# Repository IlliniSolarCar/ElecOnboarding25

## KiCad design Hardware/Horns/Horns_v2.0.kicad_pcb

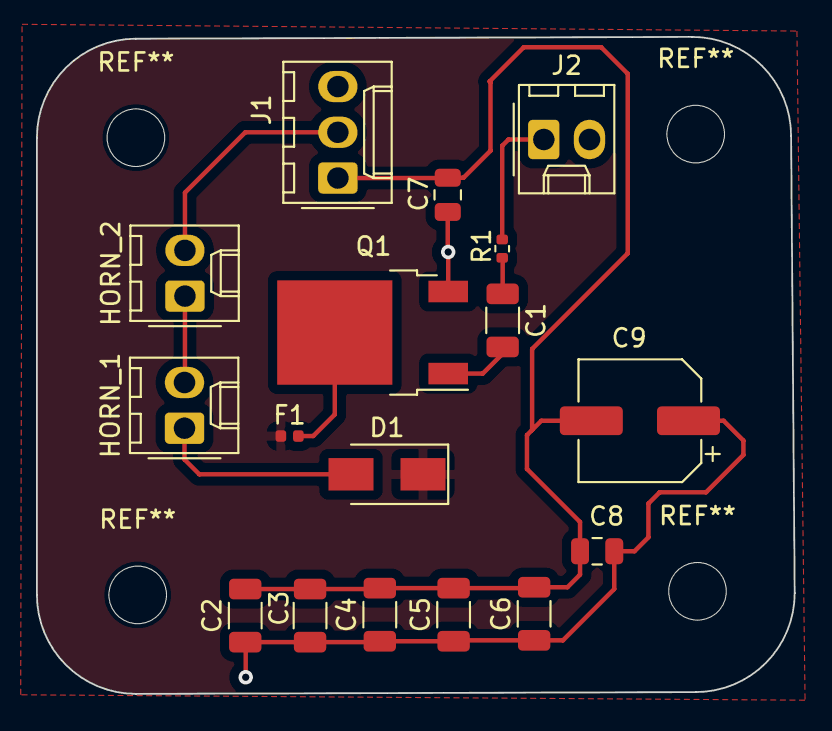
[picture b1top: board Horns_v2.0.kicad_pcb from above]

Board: 2 copper layers, 42.1 x 36.5 mm, 17 parts (0 on the bottom side), 10 nets.

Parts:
C1, C2, C3, C4: 0.1uF; C_1206_3216Metric
C5, C6: 1uF; C_1206_3216Metric
C7, C8: 10uF; C_0805_2012Metric
C9: 100uF; CP_Elec_6.3x5.4_Nichicon
D1: DIODE; D_SMA
F1: 2A; Fuse_0402_1005Metric
HORN_1, HORN_2: Conn_01x02; Molex_KK-254_AE-6410-02A_1x02_P2.54mm_Vertical
J1: Conn_01x03; Molex_KK-254_AE-6410-03A_1x03_P2.54mm_Vertical
J2: Conn_01x02; Molex_KK-254_AE-6410-02A_1x02_P2.54mm_Vertical
Q1: Q_NMOS_GDS; TO-252-2
R1: 1k; R_0402_1005Metric

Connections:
+3V3: D1.1 (K), F1.1
+24V: HORN_2.2, J1.2
/HORN_CONTR: J2.1, R1.1
GND: C2.1, C3.1, C4.1, C5.1, C6.1, C7.1, C8.1, C9.1, J1.3, J2.2, Q1.3 (S)
unnamed: C1.1, R1.2
unnamed: D1.2 (A), HORN_1.1
unnamed: HORN_1.2, HORN_2.1
unnamed: C2.2, C3.2, C4.2, C5.2, C6.2, C7.2, C8.2, C9.2, J1.1
unnamed: F1.2, Q1.2 (D)
unnamed: C1.2, Q1.1 (G)

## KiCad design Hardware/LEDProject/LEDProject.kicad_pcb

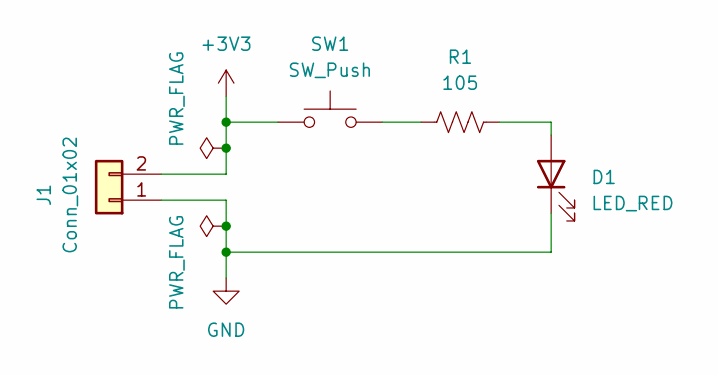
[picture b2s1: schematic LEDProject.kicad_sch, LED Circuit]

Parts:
D1: LED_RED; LED_0603_Symbol_on_F.SilkS
J1: Conn_01x02; Molex_KK-254_AE-6410-02A_1x02_P2.54mm_Vertical; MPN 22272021
R1: 105; R_0603_1608Metric_Pad0.98x0.95mm_HandSolder
SW1: SW_Push; SW_DIP_SPSTx01_Slide_6.7x4.1mm_W8.61mm_P2.54mm_LowProfile; MPN 1825910-6

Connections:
+3V3: J1.2, SW1.1
GND: D1.1 (K), J1.1
unnamed: D1.2 (A), R1.2
unnamed: R1.1, SW1.2

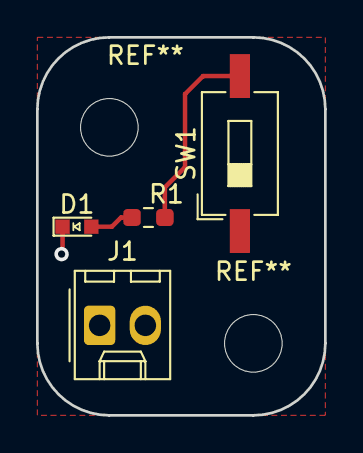
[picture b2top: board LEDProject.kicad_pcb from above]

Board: 2 copper layers, 16.0 x 21.0 mm, 4 parts (0 on the bottom side), 4 nets.
